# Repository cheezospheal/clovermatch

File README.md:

# Clovermatch
A PCB designed to play a game in order to test your reaction time and hand-eye coordination using colours!

You know that one reaction time game that gives you an amount of seconds when you "click when the screen turns green"? Or the Simon Says game where it gives you a specific pattern and you have to memorize it? Well I thought I would combine them into one game, where it'll test you on both your reaction time and hand-eye coordination! It's meant to be as easy as possible to play, not only for me to make but also for people that just want something with their friends to be competitive about. It's not just a game for yourself, more of something you can talk about with your friends and spend time trying to get better! Though it's relatively simple, it's also my first ever almost entirely custom PCB, so I'm super proud of it! :)

In the game, Clovermatch chooses a colour. Then, the player must press the button corresponding to that colour, and then Clovermatch will display the reaction time if the player was correct. If the player was wrong, the game will restart. Additionally, the LEDs and buttons change each round, so the right button is not always red every round, for example. In this way, the LEDs actually have some function in the game! <br>

## Summary
### Files
The PCB was designed using **KiCad** and the code was made with **CircuitPython** in **VS Code**. Please see the files below for what you need to import/download:
|File|What's inside?|
|---|---|
|clovermatch.kicad_pcb|contains the PCB layout, including the footprints, footprints, and edge cuts|
|clovermatch.kicad_pro|contains the project settings and configuration|
|clovermatch.kicad_sch|contains the schematic and connections|
|clovermatch_gerbers.zip|contains several gerber files|
|code.py|contains the firmware used to run the microcontroller|
|BOM.csv|Bill of Materials [Half Life]|

### External Libraries
There was also the use of several external libraries, which can be seen here:
|File/Folder|What does it do?|Link|
|---|---|---|
|adafruit_displayio_ssd1306.mpy|contains info for CircuitPython on how to initialize the OLED and draw pixels|https://github.com/adafruit/Adafruit_CircuitPython_Bundle/releases (Extract from the lib folder in the bundle)|
|adafruit_display_text|allows the OLED to display texts and fonts|https://github.com/adafruit/Adafruit_CircuitPython_Bundle/releases (Extract from the lib folder in the bundle)|
|neopixel.mpy|contains colour data formatting, array management, voltage, etc. for the NeoPixels|https://github.com/adafruit/Adafruit_CircuitPython_Bundle/releases (Extract from the lib folder in the bundle)|
|Hackclub Footprints.pretty|contains footprints, specifically for the Kailh Low Choc Switches|https://github.com/KaiPereira/Hackclub-KiCad-Libraries|
|Seeed Studio Xiao Series|contains footprints, specifically for the XIAO ESP32-C3|https://wiki.seeedstudio.com/XIAO_ESP32C3_Getting_Started/|

### Extra Resources
Here is also a list of useful links that I used (mostly just for the firmware, all in CircuitPython):
|Use|Link|
|---|---|
|bassics of the SSD1306 OLED screen|https://www.youtube.com/watch?v=nHECoycpmEY|
|displays on the OLED Screen|https://www.youtube.com/watch?v=-lrJ0fy0xm0|
|basics of NeoPixels|https://www.youtube.com/watch?v=qRyp4pKvi3g&t=300s|
|timer and use of time|https://www.youtube.com/watch?v=ZIKjZEkB48w|
|time.monotonic() and related functions|https://docs.circuitpython.org/en/latest/shared-bindings/time/|
|basics of push buttons|https://www.youtube.com/watch?v=UGaDaY-JTYU|
|how to use dictionaries|https://www.w3schools.com/python/python_dictionaries.asp|

## Schematic
The schematic is located in the clovermatch.kicad_sch file, and you'll see some points of interest. This was also mostly made by me based on information from the guide! The custom items I added are the 4 pin connector for the OLED, the switches, and back key lighting.
* [U1] XIAO Seeed Studio ESP32-C3 (microcontroller)
* [U2] 74AHCT1G125 (level shifter)
* [SW1, SW2, SW3, SW4] SW_Push (tactile push switches)
* [J2] Conn_o1x04_Pin (connecting pins for the OLED)
* [D1-D16] WS2812B (5mm * 5mm NeoPixels)
* [D17, D18, D19, D20] SK6812MINI-E (Back Key RGB LEDs)
* [C1-C21] 100nF Capacitor
* [C22] 22µF Bulk Capacitor

<br><br>
Use these pins as reference for the firmware!
<br><br>

|Pin|Part|
|---|---|
|D0|Switch 1|
|D1|Switch 2|
|D2|Switch 3|
|D4|OLED I2C SCL|
|D5|OLED I2C SDA|
|D6|LED Data Line|
|D7|Switch 4|

I also added in the footprints according to the guide, and I used the same footprints I did for my MIDI for the OLED and switches. I'm also using 5mm * 5mm NeoPixels since they'll probably be easier to solder. <br><br>

## Routing & Customization
After looking at the schematic you can take a look at the routing and customization in the PCB editor (clovermatch.kicad_pcb). I'm a beginner to PCB making so the routing is definitely messy and non-symmetrical, but I tried my best to make it work. I also added the GND pour on the back since you can then just use vias to route close to GND traces in the front, so you don't need a GND pour on both sides (the back is cleaner, so it makes more sense to have it on the back). The graphics/text were added using KiCad's built in image converter to change it to a bitmap, and then added to a custom library before being added onto F.Silkscreen as a footprint. Also, make sure to notice the image resizer that is also built into image converter!! I had lots of trouble with trying to resize my footprints since there's no way to do so in KiCad's footprint editor, so you have to use an external website (such as https://kicad-footprint-resizer.streamlit.app/). However, because this footprint's only going to be used as a graphic, you can just resize it in the image converter! Another thing to note is that it's a lot more of a hassle to make an image as a footprint than it is to make text. So I'd recommend planning out what you want on your PCB instead of just trying different things and seeing what works, since that takes a lot more time than necessary. Take advantage of the fact that you can manipulate text to appear as a graphic; for example, I used + signs stretched out to use as sparkles!
<br><br>

## Firmware
For the firmware, I coded it in VS Code using Python (though I'll test it as CircuitPython once I get the actual PCB). You can just open up the code.py in VS Code (or any other applicable software). For this, I mostly used the extra resources I outlined in the beginning, and asked a few of my real-life friends that know Python better than I do for some help with the logic errors and cleaning up the code. It may have some extra logic errors that I'll fix when I can test out the board, but here's an explanation of each part of the only 147-line piece of code.

### Libraries
```python
import board
import digitalio
import neopixel
import time
from digitalio import DigitalInOut, Direction, Pull
import terminalio
import adafruit_displayio_ssd1306
import displayio
from adafruit_display_text import label
import random
```
This section imports the specific libraries that I'll be using in the code! A great thing about CircuitPython is that you don't have to code it all from scratch, you can just assemble different parts from libraries. So, for example, it would be very difficult to try and code a NeoPixel, but, with the neopixel library, you can just use pixels[i] (pixels/your applicable onboarding)! It's super easy for beginners and I already know a little bit of Python, so I'd recommend it even for people that know nothing about code.

### Setup
```python
# sets up display
displayio.release_displays()
i2c = board.I2C()
display_bus = displayio.I2CDisplay(i2c, device_address = 0x3d)
WIDTH = 128
HEIGHT = 64
BORDER = 5

display = adafruit_displayio_ssd1306.SSD1306(display_bus, width=WIDTH, height=HEIGHT)

group = displayio.Group()
text_area = label.Label(terminalio.FONT, text = "", x=10, y=25)
group.append(text_area)
display.root_group = group

# sets up the NeoPixels
onboard_pixel = neopixel.NeoPixel(board.D6, 20, brightness=0.3, auto_write=True)

# sets up the switches
button1 = DigitalInOut(board.D0)
button1.direction = Direction.INPUT
button1.pull = Pull.UP

button2 = DigitalInOut(board.D1)
button2.direction = Direction.INPUT
button2.pull = Pull.UP

button3 = DigitalInOut(board.D2)
button3.direction = Direction.INPUT
button3.pull = Pull.UP

button4 = DigitalInOut(board.D7)
button4.direction = Direction.INPUT
button4.pull = Pull.UP

# colours
RED = (219, 95, 81)
LIGHT_RED = (247, 155, 145)
BLUE = (105, 162, 214)
LIGHT_BLUE = (166, 210, 252)
GREEN = (106, 214, 114)
LIGHT_GREEN = (158, 242, 163)
YELLOW = (242, 208, 121)
LIGHT_YELLOW = (250, 224, 175)
OFF = (0, 0, 0)
```
This setup contains everything I need to run the OLED, display text on the OLED, onboard the Neopixels, set up the switches, and set some constants for the colours. To set up the OLED, you just need to set an address to it (and make sure to clear the entire OLED before starting). The text is a little more difficult, since you have to make a group and a label inside that group that will allow you display text; I'd recommend the "displays on the OLED screen" video I put in the summary. The NeoPixels are set up with just one line of code, which is to set its pin, how many there are, brightness, and auto_write. Since I connected all my NeoPixels to each other, I don't have to worry about needing multiple onboardings. The switches are also pretty simple, the only thing you really need to add is what pin they are. The direction just states that it's an input and the pull just states that you need to pull up to not use it (i.e., you need to press down to use it). Finally, I set some constants to RGB values, as NeoPixels only read RGB values and this just makes it so I don't have to write out the whole thing each time.

### Game Loop Setup
```python
game_start = False
while game_start == False:
    if not button1.value or not button2.value or not button3.value or not button4.value:
        game_start = True
        time.sleep(0.2)
button_colour = ["red", "blue", "green", "yellow"]
colours = {
    "red": RED,
    "blue": BLUE,
    "green": GREEN,
    "yellow": YELLOW
}

light_colours = {
    "red": LIGHT_RED,
    "blue": LIGHT_BLUE,
    "green": LIGHT_GREEN,
    "yellow": LIGHT_YELLOW
}

# loop
while game_start:
    target_colour = random.choice(["red", "blue", "green", "yellow"])
    random.shuffle(button_colour)
    start_time = time.monotonic()
    iteration = True
    onboard_pixel[16] = colours[button_colour[0]]
    onboard_pixel[17] = colours[button_colour[1]]
    onboard_pixel[18] = colours[button_colour[2]]
    onboard_pixel[19] = colours[button_colour[3]]
```
This area of the code is for the actual game loop. In the first section, it waits until one of the buttons is pressed to start the game. Since the button only detects when it is pulled up, you need to use a not in front of its value to detect when it is pushed down. When any of the four are pressed, the game_start is set to True. After that, I made some dictionaries to correspond strings with RGB values. When I first made my code, I made each button store a string when pressed, and I don't know why I didn't just make it store the RGB value but I never fixed this so I just decided to make a dictionary instead. It would probably be faster for me to just replace each string, but this helps me practice a bit more, I guess? 

Once the game starts, a random target colour is selected. Then, it'll randomly shuffle the button colour set, before making each back key LED (16-19) light up to the button colour it corresponds to. It also starts the reaction timer using time.monotonic() (see the extra resources in the summary!)

### Iterations
```python
    while iteration:
        text_area.text = (f"Quick, press {target_colour}!")
        selected_colour = ""
        if not button1.value:
            for i in range(4):
                onboard_pixel[i] = light_colours[button_colour[0]]
            selected_colour = button_colour[0]
        elif not button2.value:
            for i in range(4, 8):
                onboard_pixel[i] = light_colours[button_colour[1]]
            selected_colour = button_colour[1]
        elif not button3.value:
            for i in range(8, 12):
                onboard_pixel[i] = light_colours[button_colour[2]]
            selected_colour = button_colour[2]
                
        elif not button4.value:
            for i in range(12, 16):
                onboard_pixel[i] = light_colours[button_colour[3]]
            selected_colour = button_colour[3]
        else:
            for i in range(4):
                onboard_pixel[i] = colours[button_colour[0]]
            for i in range(4, 8):
                onboard_pixel[i] = colours[button_colour[1]]
            for i in range(8, 12):
                onboard_pixel[i] = colours[button_colour[2]]
            for i in range(12, 16):
                onboard_pixel[i] = colours[button_colour[3]]
```
Clovermatch is meant to run on rounds, not just one game. This is so you don't have to restart each game just to continue playing, since each round only takes ~2 seconds. To do this, I added another while loop inside of the original game loop for each iteration. It starts by making the OLED display "Quick, press {target_colour}!". Then based on which button you press (and its corresponding button colour), it'll store that value inside of selected_colour. I also wanted to make the LEDs change in some way and not just stay static throughout the entire round, so I made it change to a lighter version of that colour when you press the button. It'll make it not only aesthetically pleasing but also allow you to see what colour you chose in case you forget and rage quit if you think the game is wrong. 

### Reaction Time Check
```python
        if selected_colour != "":
            reaction_time = time.monotonic() - start_time
            if selected_colour == target_colour:
                text_area.text = f"Time: {reaction_time}\n"
                if reaction_time > 0.600:
                    text_area.text = "If you didn't know, you're supposed to be quick!"
                elif 0.400 < reaction_time <= 0.600:
                    text_area.text = "Try a little faster?"
                elif 0.300 < reaction_time <= 0.400:
                    text_area.text = "A little slower than average."
                elif 0.273 < reaction_time <= 0.300:
                    text_area.text = "Perfectly average!"
                elif 0.250 < reaction_time <= 0.273:
                    text_area.text = "A little faster than average."
                elif 0.200 < reaction_time <= 0.250:
                    text_area.text = "Nice and quick!"
                elif 0.180 < reaction_time <= 0.200:
                    text_area.text = "Faster than a cheetah!"
                elif 0.150 < reaction_time <= 0.180:
                    text_area.text = "Are you trained for this?"
                elif reaction_time <= 0.150:
                    text_area.text = "Are you sure you aren't cheating?"
                time.sleep(1)
            else:
                game_start = False
                text_area.text = "Wrong colour!"
                time.sleep(1)
            iteration = False
```
The final part of the code is to tell you what your reaction time was and then restart the round or game. The reaction time is simply calculated using the difference between the current time and the start time, which gives the time elapsed. It detects once you have chosen a colour by detecting whether or not your selected colour is empty. If you get the colour correct, it'll display your reaction time and a cute little message based on how fast you were! Those times are solely based on average reaction times, however, so I'll probably need to change the values and do some of my own testing to account for having to think about which colour to press and your hand-eye coordination. If you get the colour wrong, it'll just display "Wrong colour!" before restarting the game. 

## Bill of Materials
Please note that this BOM is for general users! For Half Life, please view the BOM submitted on the Half Life website. Also note that these prices are given without any special discounts, but AliExpress often gives discounts anyways, so prices are probably cheaper than shown. Shipping is based off my own address and the tax is calculated with the Ontario rate of 13%.

|Part|Price (USD)|Quantity|Vendor|Link|
|---|---|---|---|---|
|XIAO Seeed Studio ESP32-C3|$4.47|1|AliExpress|https://www.aliexpress.com/item/1005008791937363.html?spm=a2g0o.cart.0.0.284238daZvshSH&mp=1&pdp_npi=6%40dis%21CAD%21CAD+13.16%21CAD+11.00%21%21CAD+11.00%21%21%21%40210327ef17935643738446320e103a%2112000052930246742%21ct%21CA%218338085966%21%211%210%21|
|SK6812 RGB LEDs|$2.61|1|AliExpress|https://www.aliexpress.com/item/1005007863635868.html?spm=a2g0o.productlist.main.1.467e66echpig2D&algo_pvid=17f43b4a-c6ec-4e01-9861-3f38f1696518&algo_exp_id=17f43b4a-c6ec-4e01-9861-3f38f1696518-0&pdp_ext_f=%7B%22order%22%3A%22641%22%2C%22eval%22%3A%221%22%2C%22fromPage%22%3A%22search%22%7D&pdp_npi=6%40dis%21CAD%216.71%211.42%21%21%214.68%210.99%21%402101c69517929046052793291e0d52%2112000042594617264%21sea%21CA%218338085966%21ABX%211%210%21n_tag%3A-29910%3Bd%3Ac42caa26%3Bm03_new_user%3A-29895%3BpisId%3A5000000218625932&curPageLogUid=AQFVQ5jQSkKF&utparam-url=scene%3Asearch%7Cquery_from%3A%7Cx_object_id%3A1005007863635868%7C_p_origin_prod%3A|
|330Ω Resistor|$2.11|1|Sayal Electronics|https://secure.sayal.com/STORE4/prodetails.php?SKU=198449|
|Kailh Low Choc Key Switches|$7.99|1|AliExpress|https://www.aliexpress.com/item/1005008883418065.html?spm=a2g0o.productlist.main.1.1c9e5913F8kBSt&algo_pvid=278c7c25-9ab1-4a2a-9760-88be0dc0cf20&algo_exp_id=278c7c25-9ab1-4a2a-9760-88be0dc0cf20-0&pdp_ext_f=%7B%22order%22%3A%221409%22%2C%22spu_best_type%22%3A%22price%22%2C%22eval%22%3A%221%22%2C%22fromPage%22%3A%22search%22%7D&pdp_npi=6%40dis%21CAD%2111.19%212.96%21%21%217.81%212.07%21%402101c69517929071229613399e0f00%2112000047082945007%21sea%21CA%218338085966%21ABX%211%210%21n_tag%3A-29910%3Bd%3Ac42caa26%3Bm03_new_user%3A-29895%3BpisId%3A5000000218625932&curPageLogUid=Vd6zfVEWhxYp&utparam-url=scene%3Asearch%7Cquery_from%3A%7Cx_object_id%3A1005008883418065%7C_p_origin_prod%3A|
|Low Choc Kailh Key Caps|$4.01|AliExpress|1|https://www.aliexpress.com/item/1005006734545486.html?spm=a2g0o.cart.0.0.e95238dafhFbxx&mp=1&pdp_npi=6%40dis%21CAD%21CAD+6.09%21CAD+1.70%21%21CAD+1.70%21%21%21%402101d33417935618930793539e0e8c%2112000044697706461%21ct%21CA%218338085966%21%211%210%21&pdp_ext_f=%7B%22cart2PdpParams%22%3A%7B%22pdpBusinessMode%22%3A%22retail%22%7D%7D|
|128 x 64 0.96" OLED|$2.51|AliExpress|1|https://www.aliexpress.com/item/1005005462085489.html?spm=a2g0o.productlist.main.1.38bc2365vp9GcI&algo_pvid=6d367ac4-7b02-4b22-ba6b-ba9d2b3a06f9&algo_exp_id=6d367ac4-7b02-4b22-ba6b-ba9d2b3a06f9-0&pdp_ext_f=%7B%22order%22%3A%22462%22%2C%22spu_best_type%22%3A%22price%22%2C%22eval%22%3A%221%22%2C%22fromPage%22%3A%22search%22%7D&pdp_npi=6%40dis%21CAD%214.34%211.71%21%21%213.03%211.19%21%40210303cd17929073709107426e0c72%2112000049496537372%21sea%21CA%218338085966%21ABX%211%210%21n_tag%3A-29910%3Bd%3Ac42caa26%3Bm03_new_user%3A-29895%3BpisId%3A5000000218656158&curPageLogUid=9Jwm7mz2IcVf&utparam-url=scene%3Asearch%7Cquery_from%3A%7Cx_object_id%3A1005005462085489%7C_p_origin_prod%3A|
|74AHCT125N Level Shifter|$2.26|1|AliExpress|https://www.aliexpress.com/item/1005007655828920.html?spm=a2g0o.productlist.main.2.26b7551ew076eH&algo_pvid=78c66c40-76f2-432e-87b2-bd3bfed3491f&algo_exp_id=78c66c40-76f2-432e-87b2-bd3bfed3491f-1&pdp_ext_f=%7B%22order%22%3A%222562%22%2C%22spu_best_type%22%3A%22price%22%2C%22eval%22%3A%221%22%2C%22fromPage%22%3A%22search%22%7D&pdp_npi=6%40dis%21CAD%213.50%211.41%21%21%212.45%210.99%21%402103081117935628901173779e0e93%2112000041675151148%21sea%21CA%218338085966%21ABX%211%210%21n_tag%3A-29910%3Bd%3A251db7%3Bm03_new_user%3A-29895%3BpisId%3A5000000218625936&curPageLogUid=agilp282nRvO&utparam-url=scene%3Asearch%7Cquery_from%3A%7Cx_object_id%3A1005007655828920%7C_p_origin_prod%3A|
|22uF Bulk Capacitor|$2.96|1|AliExpress|https://www.aliexpress.com/item/1005007464553853.html?spm=a2g0o.cart.0.0.36d438dalcLke0&mp=1&pdp_npi=6%40dis%21CAD%21CAD+9.00%21CAD+1.70%21%21CAD+1.70%21%21%21%40210327ef17935644201098839e103a%2112000040865339146%21ct%21CA%218338085966%21%211%210%21|
|100nF Capacitor|$3.32|1|AliExpress|https://www.aliexpress.com/item/1005003512666695.html?spm=a2g0o.productlist.main.3.83c45afbDEEDUU&algo_pvid=ef56e91d-e1a5-43da-841c-f11ec07990dc&algo_exp_id=ef56e91d-e1a5-43da-841c-f11ec07990dc-2&pdp_ext_f=%7B%22order%22%3A%22202%22%2C%22spu_best_type%22%3A%22price%22%2C%22eval%22%3A%221%22%2C%22fromPage%22%3A%22search%22%7D&pdp_npi=6%40dis%21CAD%213.77%213.31%21%21%212.64%212.32%21%40210327ef17935650993205568e109d%2112000026121796491%21sea%21CA%218338085966%21ABX%211%210%21n_tag%3A-29910%3Bd%3A251db7%3Bm03_new_user%3A-29895%3BpisId%3A5000000220770329&curPageLogUid=wUzDEXA1trVM&utparam-url=scene%3Asearch%7Cquery_from%3A%7Cx_object_id%3A1005003512666695%7C_p_origin_prod%3A|
|PCB|$4.00|1|JLCPCB|https://jlcpcb.com/|
|Shipping & Taxes|-||$1.77|-|
|Total|-|-|$36.24|-|

## Extra Notes 
Note that, for the cart screenshots submitted on the Half Life website, all prices are in CAD. However, all prices have been converted for each individual item into USD for the BOM, thus there may be a small rounding error (will most likely be negligible; I can pay the difference out of pocket). There is 1 cart screenshot labeled [ALREADY OWNED] that displays the cart of the items I already own, so the prices for every item in there are not counted. Furthermore, there are special discounts (specifically for AliExpress) located in the BOM.csv from Half Life, which is why I am able to afford it under the $30 budget. Additionally, a lot of the parts in the BOM.csv are priced at $0.01 because I already own them. This is because the parts are the exact parts I will be using in my Week 3 project, so I can just reuse the excess in this project and save on having to buy completely new parts. 

Please pay attention to the descriptions of each item! Those that are labeled with [OUT OF POCKET] and [ALREADY OWNED] are not purchased with the grant and thus cost $0.01. Additionally, the vendors labeled (Local) are local to me, so I do not have to pay for shipping as I can go to them in person. All shipping prices are based on my own address and ability to go in-person for certain vendors.

This was my first ever basically-entirely-custom PCB! I'm super excited to actually get to use it :)

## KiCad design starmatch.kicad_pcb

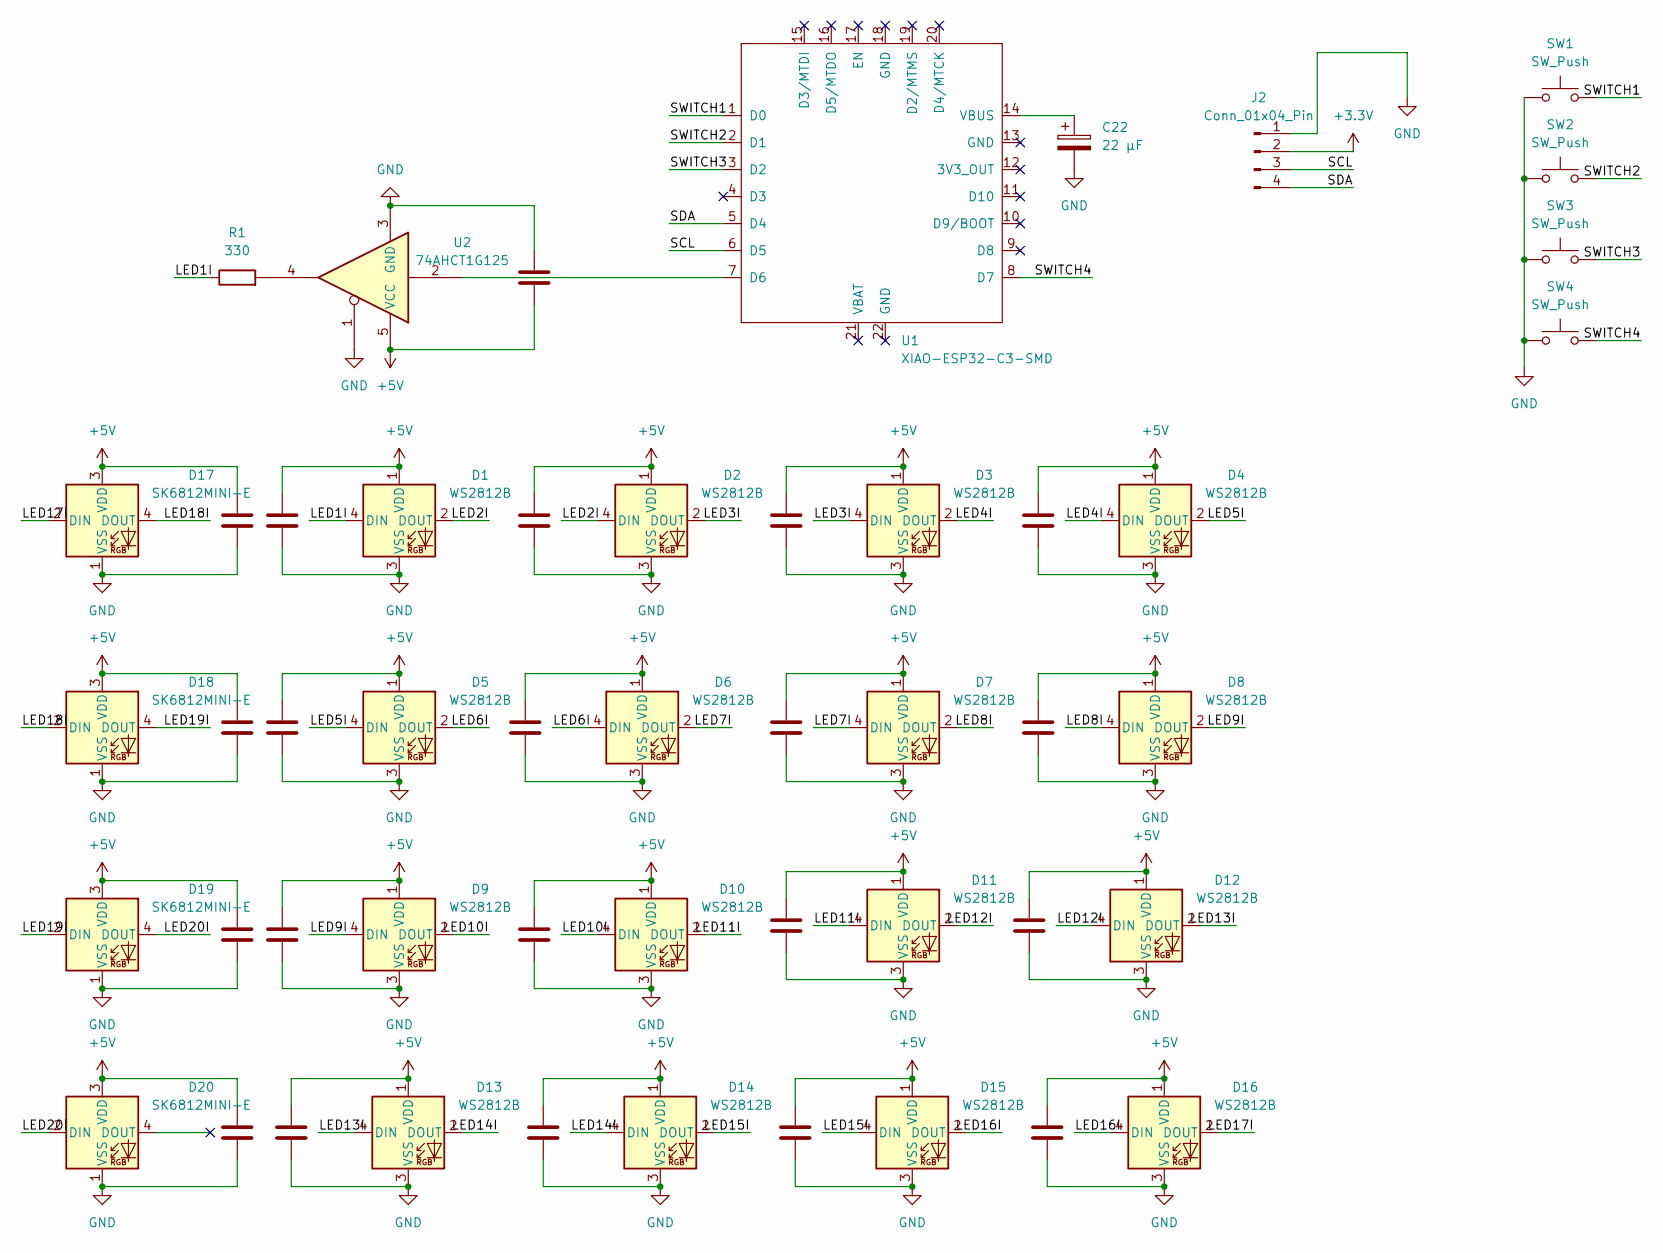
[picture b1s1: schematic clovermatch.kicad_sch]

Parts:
C1, C2, C3, C4, C5, C6, C7, C8, C9, C10, C11, C12, C13, C14, C15, C16, C17, C18, C19, C20, C21: 100nF; C_0603_1608Metric
C22: 22 µF; C_0805_2012Metric
D1, D2, D3, D4, D5, D6, D7, D8, D9, D10, D11, D12, D13, D14, D15, D16: WS2812B; LED_WS2812B_PLCC4_5.0x5.0mm_P3.2mm
D17, D18, D19, D20: SK6812MINI-E; LED_SK6812MINI-E_3.2x2.8mm_P1.5mm_ReverseMount
J2: Conn_01x04_Pin; FanPinHeader_1x04_P2.54mm_Vertical
R1: 330; R_0603_1608Metric
SW1, SW2, SW3, SW4: SW_Push; Kailh Choc Low-Profile Switches
U1: XIAO-ESP32-C3-SMD
U2: 74AHCT1G125; SOT-23-5

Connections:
+3.3V: J2.2
+5V: C1.2, C2.2, C3.2, C4.2, C5.2, C6.2, C7.2, C8.2, C9.2, C10.2, C11.2, C12.2, C13.2, C14.2, C15.2, C16.2, C17.2, C18.2, C19.2, C20.2, C21.2, D1.1 (VDD), D2.1 (VDD), D3.1 (VDD), D4.1 (VDD), D5.1 (VDD), D6.1 (VDD), D7.1 (VDD), D8.1 (VDD), D9.1 (VDD), D10.1 (VDD), D11.1 (VDD), D12.1 (VDD), D13.1 (VDD), D14.1 (VDD), D15.1 (VDD), D16.1 (VDD), D17.3 (VDD), D18.3 (VDD), D19.3 (VDD), D20.3 (VDD), U2.5 (VCC)
/LED1I: D1.4 (DIN), R1.1
/LED2I: D1.2 (DOUT), D2.4 (DIN)
/LED3I: D2.2 (DOUT), D3.4 (DIN)
/LED4I: D3.2 (DOUT), D4.4 (DIN)
/LED5I: D4.2 (DOUT), D5.4 (DIN)
/LED6I: D5.2 (DOUT), D6.4 (DIN)
/LED7I: D6.2 (DOUT), D7.4 (DIN)
/LED8I: D7.2 (DOUT), D8.4 (DIN)
/LED9I: D8.2 (DOUT), D9.4 (DIN)
/LED10I: D9.2 (DOUT), D10.4 (DIN)
/LED11I: D10.2 (DOUT), D11.4 (DIN)
/LED12I: D11.2 (DOUT), D12.4 (DIN)
/LED13I: D12.2 (DOUT), D13.4 (DIN)
/LED14I: D13.2 (DOUT), D14.4 (DIN)
/LED15I: D14.2 (DOUT), D15.4 (DIN)
/LED16I: D15.2 (DOUT), D16.4 (DIN)
/LED17I: D16.2 (DOUT), D17.2 (DIN)
/LED18I: D17.4 (DOUT), D18.2 (DIN)
/LED19I: D18.4 (DOUT), D19.2 (DIN)
/LED20I: D19.4 (DOUT), D20.2 (DIN)
/SCL: J2.3, U1.6 (D5)
/SDA: J2.4, U1.5 (D4)
/SWITCH1: SW1.2, U1.1 (D0)
/SWITCH2: SW2.2, U1.2 (D1)
/SWITCH3: SW3.2, U1.3 (D2)
/SWITCH4: SW4.2, U1.8 (D7)
GND: C1.1, C2.1, C3.1, C4.1, C5.1, C6.1, C7.1, C8.1, C9.1, C10.1, C11.1, C12.1, C13.1, C14.1, C15.1, C16.1, C17.1, C18.1, C19.1, C20.1, C21.1, C22.2, D1.3 (VSS), D2.3 (VSS), D3.3 (VSS), D4.3 (VSS), D5.3 (VSS), D6.3 (VSS), D7.3 (VSS), D8.3 (VSS), D9.3 (VSS), D10.3 (VSS), D11.3 (VSS), D12.3 (VSS), D13.3 (VSS), D14.3 (VSS), D15.3 (VSS), D16.3 (VSS), D17.1 (VSS), D18.1 (VSS), D19.1 (VSS), D20.1 (VSS), J2.1, SW1.1, SW2.1, SW3.1, SW4.1, U2.1, U2.3 (GND)
unnamed: R1.2, U2.4
unnamed: U1.7 (D6), U2.2
unnamed: C22.1, U1.14 (VBUS)

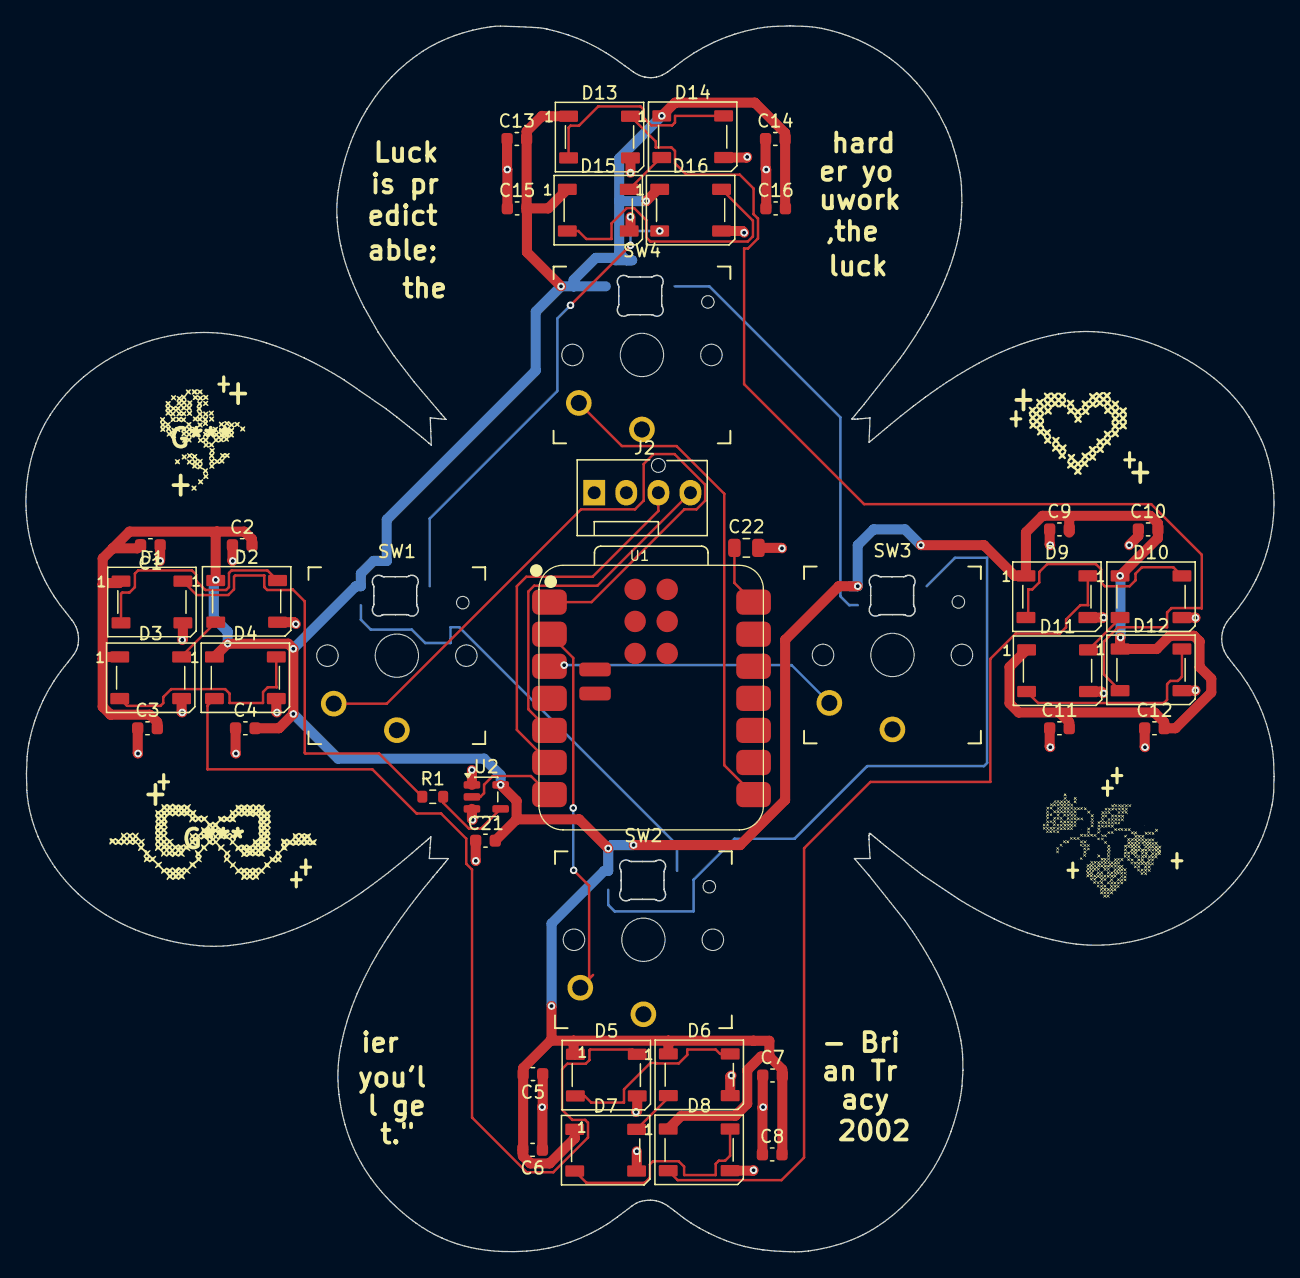
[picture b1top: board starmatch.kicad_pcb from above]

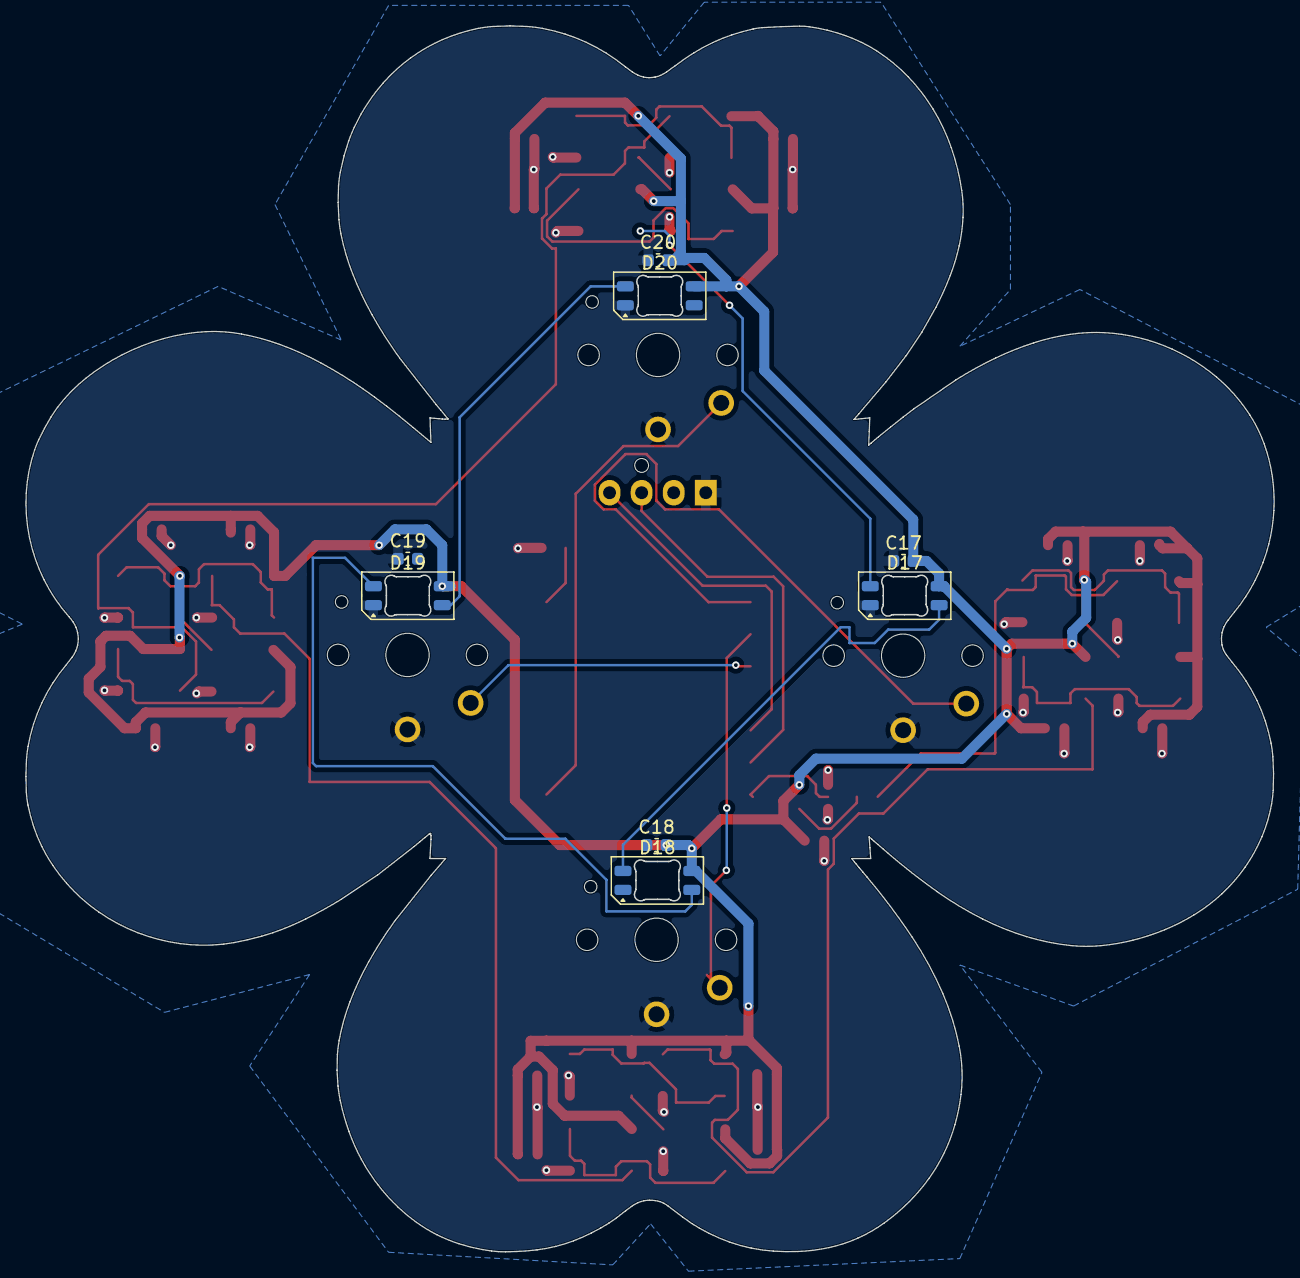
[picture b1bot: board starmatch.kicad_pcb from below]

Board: 2 copper layers, 98.9 x 97.1 mm, 50 parts (8 on the bottom side), 31 nets.
